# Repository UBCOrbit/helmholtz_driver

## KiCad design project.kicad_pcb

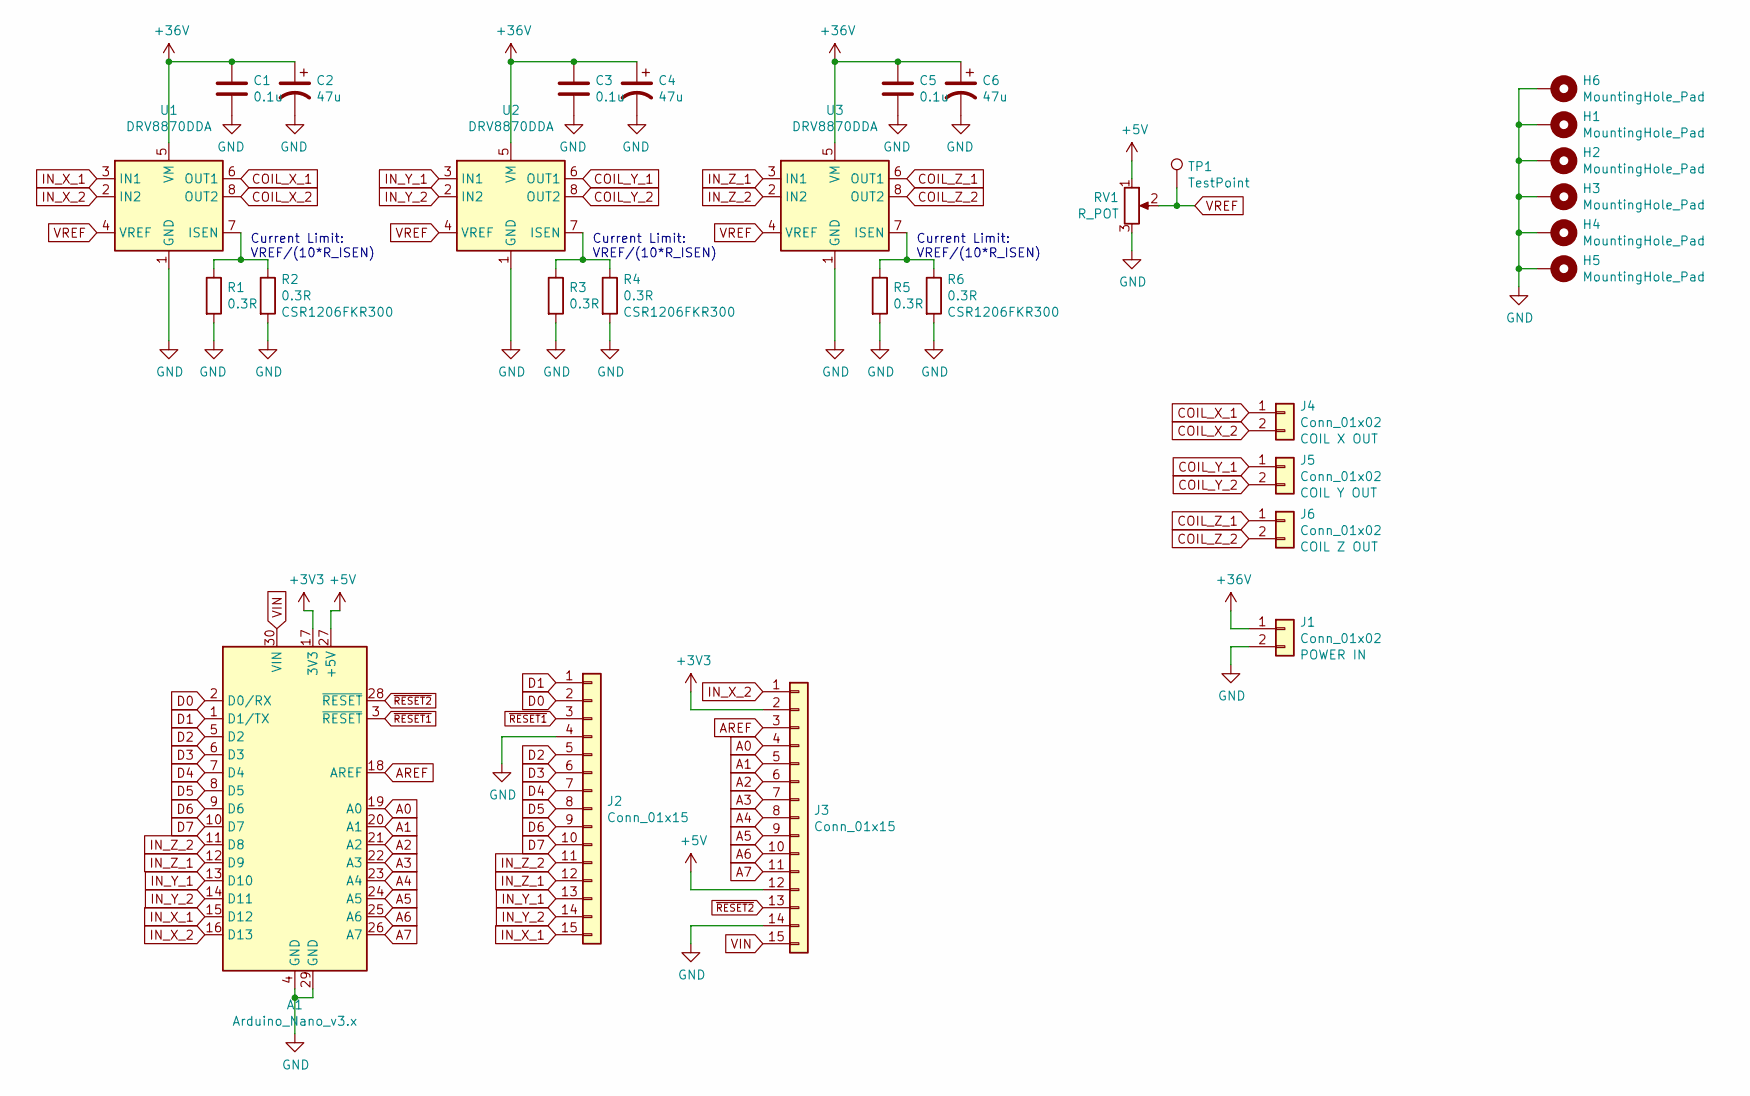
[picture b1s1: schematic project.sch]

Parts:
A1: Arduino_Nano_v3.x; Arduino_Nano
C1, C3, C5: 0.1u; C_0603_1608Metric; Part Number C0603C104M5RACTU
C2, C4, C6: 47u; CP_Elec_6.3x5.4_Nichicon; Part Number UWT1H470MCL1GS
H1, H2, H3, H4, H5, H6: MountingHole_Pad; MountingHole_3.2mm_M3_Pad
J1, J4, J5, J6: Conn_01x02; Altech_AK300_1x02_P5.00mm_45-Degree
J2, J3: Conn_01x15; PinHeader_1x15_P2.54mm_Vertical
R1, R3, R5: 0.3R; R_1206_3216Metric
R2, R4, R6: 0.3R; R_1206_3216Metric; Part Number CSR1206FKR300
RV1: R_POT; Potentiometer_Bourns_3266W_Vertical
TP1: TestPoint; TestPoint_Pad_D2.0mm
U1, U2, U3: DRV8870DDA; Texas_HTSOP-8-1EP_3.9x4.9mm_P1.27mm_EP2.95x4.9mm_Mask2.4x3.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

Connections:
+3V3: A1.17 (3V3), J3.2
+5V: A1.27 (+5V), J3.12, RV1.1
+36V: C1.1, C2.1, C3.1, C4.1, C5.1, C6.1, J1.1, U1.5 (VM), U2.5 (VM), U3.5 (VM)
A0: A1.19 (A0), J3.4
A1: A1.20 (A1), J3.5
A2: A1.21 (A2), J3.6
A3: A1.22 (A3), J3.7
A4: A1.23 (A4), J3.8
A5: A1.24 (A5), J3.9
A6: A1.25 (A6), J3.10
A7: A1.26 (A7), J3.11
AREF: A1.18 (AREF), J3.3
COIL_X_1: J4.1, U1.6 (OUT1)
COIL_X_2: J4.2, U1.8 (OUT2)
COIL_Y_1: J5.1, U2.6 (OUT1)
COIL_Y_2: J5.2, U2.8 (OUT2)
COIL_Z_1: J6.1, U3.6 (OUT1)
COIL_Z_2: J6.2, U3.8 (OUT2)
D0: A1.2 (D0/RX), J2.2
D1: A1.1 (D1/TX), J2.1
D2: A1.5 (D2), J2.5
D3: A1.6 (D3), J2.6
D4: A1.7 (D4), J2.7
D5: A1.8 (D5), J2.8
D6: A1.9 (D6), J2.9
D7: A1.10 (D7), J2.10
GND: A1.4 (GND), A1.29 (GND), C1.2, C2.2, C3.2, C4.2, C5.2, C6.2, H1.1, H2.1, H3.1, H4.1, H5.1, H6.1, J1.2, J2.4, J3.14, R1.2, R2.2, R3.2, R4.2, R5.2, R6.2, RV1.3, U1.1 (GND), U1.9 (GND), U2.1 (GND), U2.9 (GND), U3.1 (GND), U3.9 (GND)
IN_X_1: A1.15 (D12), J2.15, U1.3 (IN1)
IN_X_2: A1.16 (D13), J3.1, U1.2 (IN2)
IN_Y_1: A1.13 (D10), J2.13, U2.3 (IN1)
IN_Y_2: A1.14 (D11), J2.14, U2.2 (IN2)
IN_Z_1: A1.12 (D9), J2.12, U3.3 (IN1)
IN_Z_2: A1.11 (D8), J2.11, U3.2 (IN2)
unnamed: R1.1, R2.1, U1.7 (ISEN)
unnamed: R3.1, R4.1, U2.7 (ISEN)
unnamed: R5.1, R6.1, U3.7 (ISEN)
VIN: A1.30 (VIN), J3.15
VREF: RV1.2, TP1.1, U1.4 (VREF), U2.4 (VREF), U3.4 (VREF)
~RESET1: A1.3 (~RESET), J2.3
~RESET2: A1.28 (~RESET), J3.13

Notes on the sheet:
Current Limit: VREF/(10*R_ISEN)

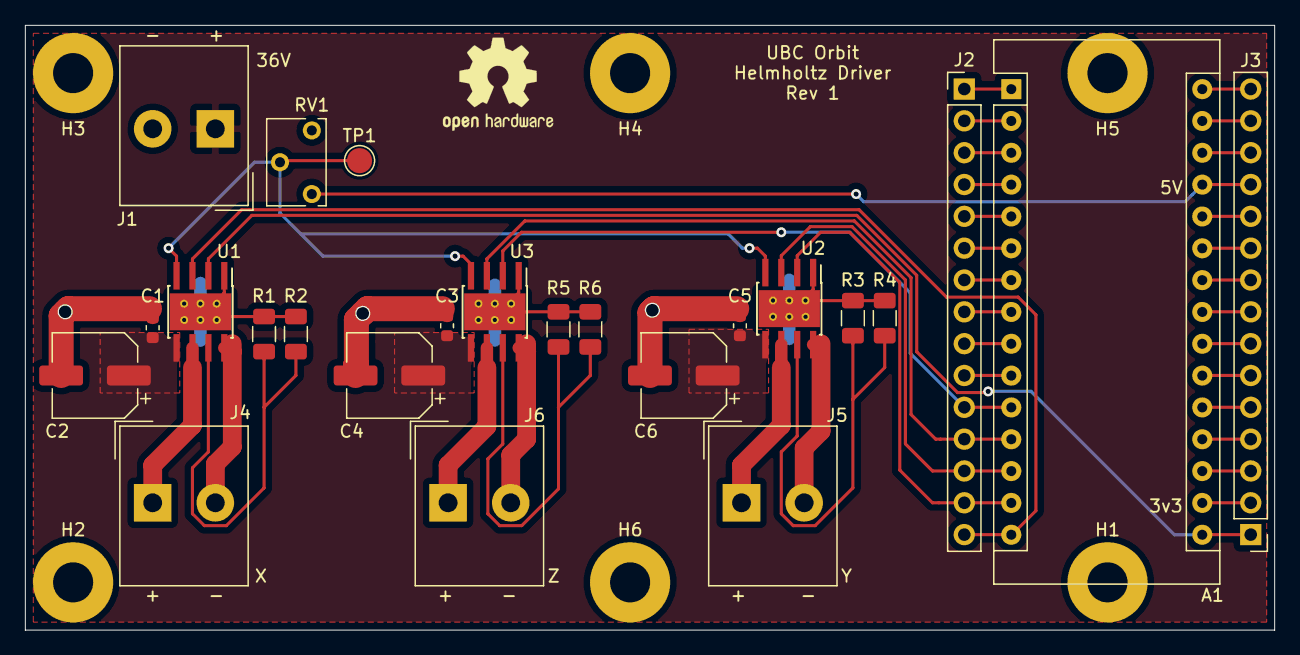
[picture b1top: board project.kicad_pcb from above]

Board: 2 copper layers, 99.7 x 48.3 mm, 30 parts (0 on the bottom side), 40 nets.

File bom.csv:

Reference, Quantity, Value, Footprint, Datasheet, Mouser, Purpose, Digikey, Part Number, Notes
A1 ,1,Arduino_Nano_v3.x,Module:Arduino_Nano,http://www.mouser.com/pdfdocs/Gravitech_Arduino_Nano3_0.pdf,,,https://www.digikey.ca/product-detail/en/sullins-connector-s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,,"Digikey link is for female headers to connect to arduino, get 2 if we don't have any lying around"
C1 C3 C5 ,3,0.1u,Capacitor_SMD:C_0603_1608Metric,~,,,https://www.digikey.com/product-detail/en/kemet/C0603C104M5R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,C0603C104M5RACTU,
C2 C4 C6 ,3,47u,Capacitor_SMD:CP_Elec_6.3x5.4_Nichicon,~,,,https://www.digikey.com/product-detail/en/nichicon/UWT1H470M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,UWT1H470MCL1GS,
H1 H2 H3 H4 H5 H6 ,6,MountingHole_Pad,MountingHole:MountingHole_3.2mm_M3_Pad,~,,,,,
J1 J4 J5 J6 ,4,Conn_01x02,TerminalBlock_Altech:Altech_AK300_1x02_P5.00mm_45-Degree,~,https://www.mouser.ca/ProductDetail/Altech/30602?qs=sGAEpiMZ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,POWER IN,,,
J2 J3 ,2,Conn_01x15,Connector_PinHeader_2.54mm:PinHeader_1x15_P2.54mm_Vertical,~,,,https://www.digikey.ca/product-detail/en/adam-tech/PH1-15-UA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,,
R2 R1 R4 R3 R6 R5 ,6,0.3R,Resistor_SMD:R_1206_3216Metric,~,,,https://www.digikey.com/product-detail/en/stackpole-electron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,CSR1206FKR300,
RV1 ,1,R_POT,Potentiometer_THT:Potentiometer_Bourns_3266W_Vertical,~,,,https://www.digikey.ca/product-detail/en/bourns-inc/3266W-1-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,,
TP1 ,1,TestPoint,TestPoint:TestPoint_Pad_D2.0mm,~,,,,,
U1 U2 U3 ,3,DRV8870DDA,Package_SO:Texas_HTSOP-8-1EP_3.9x4.9mm_P1.27mm_EP2.95x4.9mm_Mask2.4x3.1mm_ThermalVias,http://www.ti.com/lit/ds/symlink/drv8870.pdf,,,https://www.digikey.com/product-detail/en/texas-instruments/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,,

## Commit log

2020-02-14 First commit, implementation/layout done
2020-02-14 Add labels to terminal blocks
2020-02-24 Replace 36V input to drivers with solid fill
2020-02-24 Convert board to 2 layer
2020-02-24 Remove thermal reliefs on 36V nets
2020-03-04 Add bom
2020-03-04 Fix bom formatting
2020-03-13 Shorten board width
